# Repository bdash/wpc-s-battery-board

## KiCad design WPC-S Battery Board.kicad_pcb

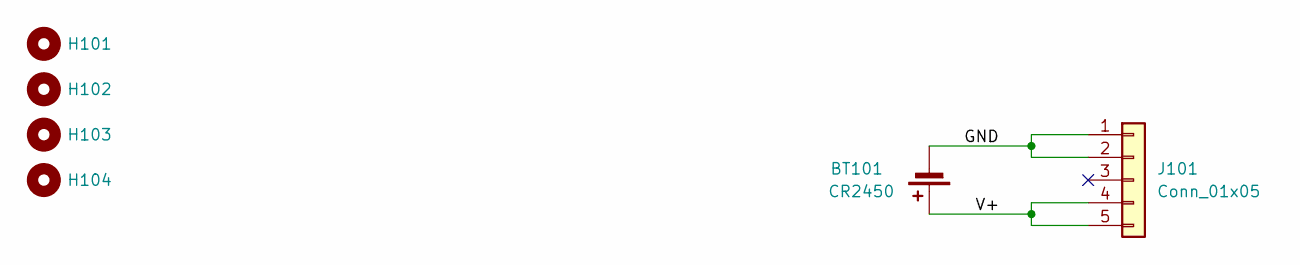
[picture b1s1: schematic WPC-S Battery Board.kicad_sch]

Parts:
BT101: CR2450; BU2450SM-JJ-GTR_MPD
H101, H102, H103, H104: MountingHole; MountingHole_4.8mm_bdash
J101: Conn_01x05; Molex_SL_171971-0005_1x05_P2.54mm_Vertical

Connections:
/GND: BT101.2 (-), J101.1, J101.2
/V+: BT101.1 (+), J101.4, J101.5

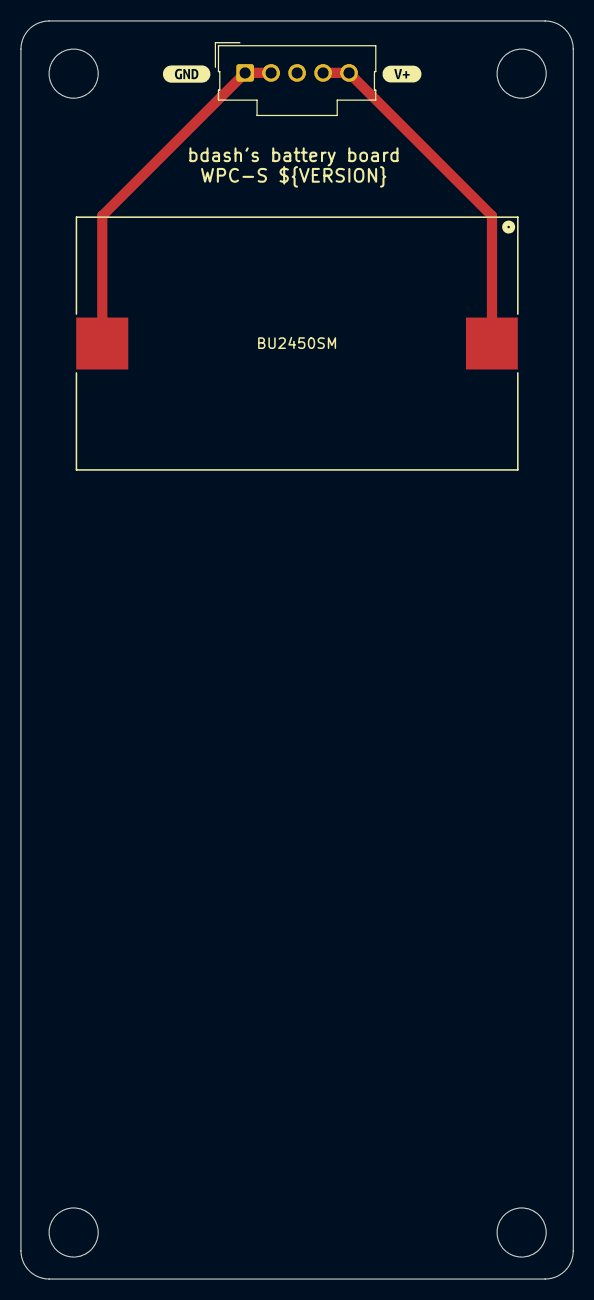
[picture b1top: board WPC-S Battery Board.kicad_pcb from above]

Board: 2 copper layers, 54.0 x 123.0 mm, 8 parts (0 on the bottom side), 2 nets.

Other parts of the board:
kibuzzard-65B0A4DC: G***; kibuzzard-65B0A4DC
kibuzzard-65B0A4FA: G***; kibuzzard-65B0A4FA

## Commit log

2024-01-24 Initial project
2024-01-24 Initial version
2024-01-24 Update GitHub actions to support small PCB variant
2024-01-24 Avoid warnings about relying on deprecated versions of the node runtime
2024-01-24 Specify JLC order number location
2024-01-31 Copper fills to make the board look nicer.
